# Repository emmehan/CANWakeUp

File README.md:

Work in progress

# CAN WakeUp

The intendation of this project is to create a device that will act as a Wake-Up source for CAN devices.
A microcontroller ([STM32F103](https://www.st.com/en/microcontrollers/stm32f103c8.html)) sends a cyclic CAN messages using an external CAN transceiver ([TJA1050](https://www.nxp.com/docs/en/data-sheet/TJA1050.pdf)).

This project includes the EAGLE schematic and layout files among the source code for the microcontroller.

# Project structure

## Hardware
@TODO

## Software
Big shout-out to Patrik Jaworski for his [blog post](http://regalis.com.pl/en/arm-cortex-stm32-gnulinux/) about the initial bring up of the STM32Fx.
It really helped me to get back on track after a longer absence from the STM32 device family.

The software is based on the [STM32CubeF1 MCu Package ](https://www.st.com/en/embedded-software/stm32cubef1.html) from ST Microelectronis.
The application software is based on the ARM CMSIS library for the STM32F103C8T6 device.

It is developed on Linux (Arch-Linux, Kernel 4.19.2) using the GNU ARM toolchain(gcc-arm-none-eabi-*).

---

### Build

To build the firmware run:

    make -C ./Software MAIN=FW_NAME
in directory.

The `MAIN` parameter is optional and used to define the firmware name.

It defaults to `CANWakeUp`.

---

### Flash

To flash the firmare to the controller run:

    openocd -f interface/stlink-v2-1.cfg -f target/stm32f1x.cfg -c "program ./build/$FW_NAME.hex  verify reset exit"
while substitute `$FW_NAME` to the correct firmware filename.

There are preconfigured tasks for Visual Studio Code available for Building, Cleaning, Flashing and Debugging (using the [Cortex-Debug](https://marcelball.ca/projects/cortex-debug) extension by marus25).

---

### Software Documentation

To build the documentation run (requires [Doxygen](http://doxygen.nl/)):

    make doc

The documentation will then be available in `./doc/html/index.html`.

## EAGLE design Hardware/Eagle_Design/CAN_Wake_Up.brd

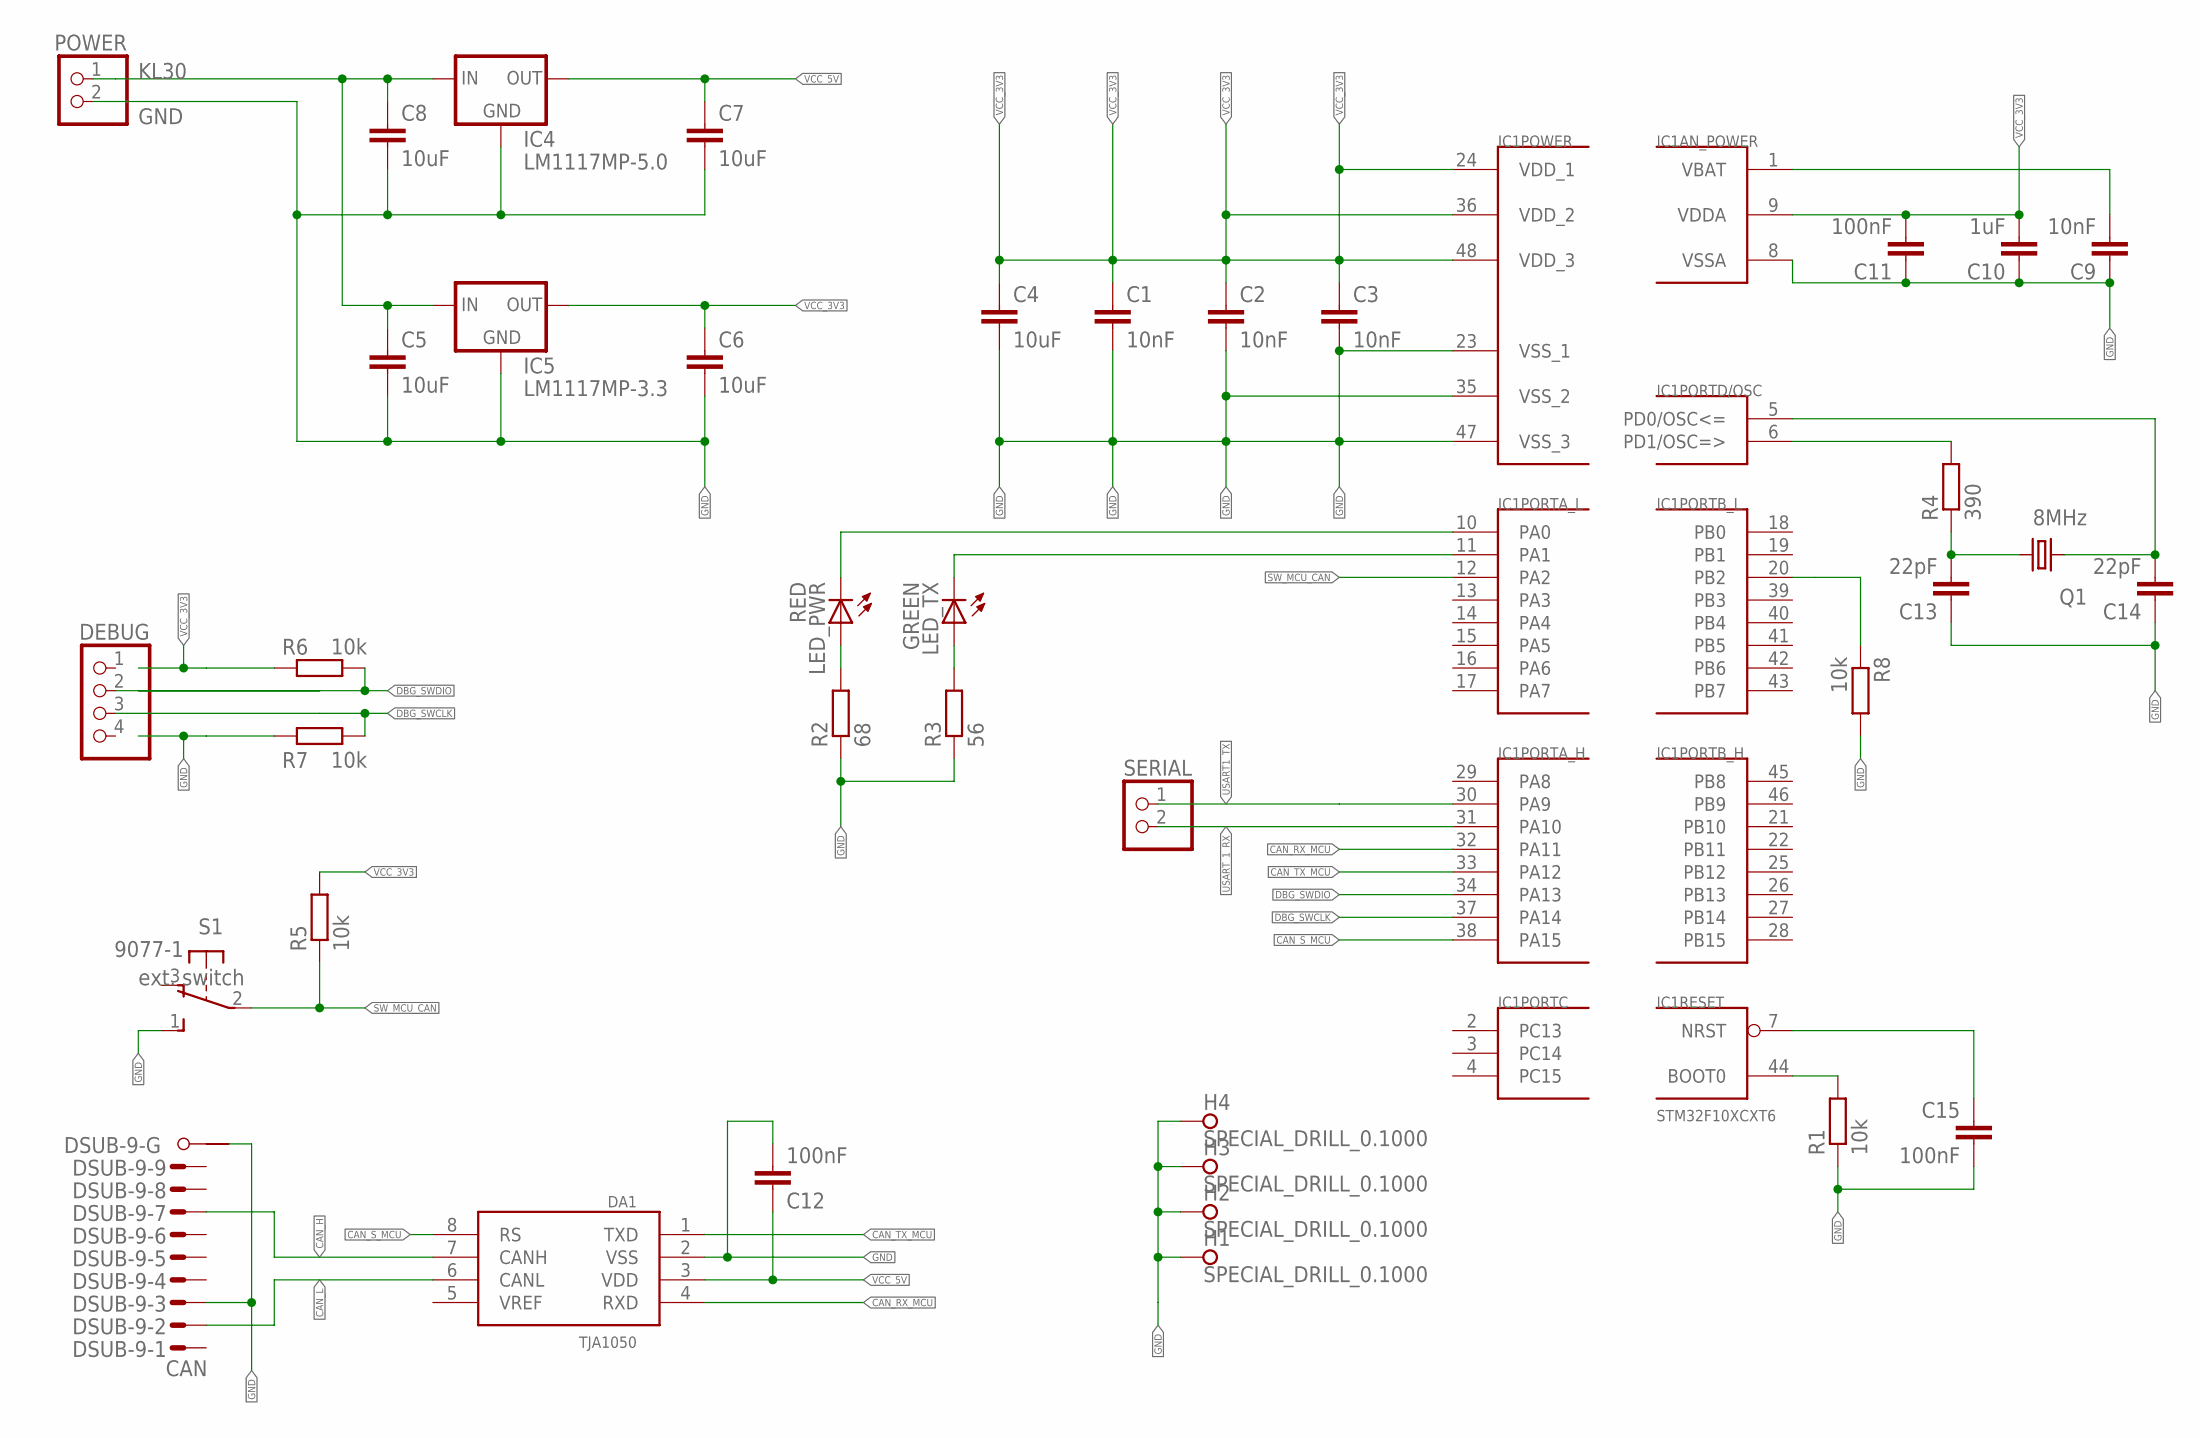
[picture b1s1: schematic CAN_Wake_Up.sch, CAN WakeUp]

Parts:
C1, C2, C3, C9: 10nF; C0805
C4, C5, C6, C7, C8: 10uF; C0805
C10: 1uF; C0805
C11, C12, C15: 100nF; C0805
C13, C14: 22pF; C0805
DA1: TJA1050; SO08
DEBUG: PINHD-1X4; 1X04
DSUB-9: CAN; M09HP
H1, H2, H3, H4: SPECIAL_DRILL_0.1000; PAD_0.1000
IC1: STM32F10XCXT6; TQFP48
IC4: LM1117MP-5.0; SOT223
IC5: LM1117MP-3.3; SOT223
LED_PWR: RED; SML0805
LED_TX: GREEN; SML0805
POWER: PINHD-1X2; 1X02
Q1: 8MHz; HC49UP
R1, R5, R6, R7, R8: 10k; R0805
R2: 68; R0805
R3: 56; R0805
R4: 390; R0805
S1: 9077-1
SERIAL: PINHD-1X2; 1X02

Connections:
CAN_H: DA1.7 (CANH), DSUB-9.7 (M)
CAN_L: DA1.6 (CANL), DSUB-9.2 (M)
CAN_RX_MCU: DA1.4 (RXD), IC1.32 (PA11)
CAN_S_MCU: DA1.8 (RS), IC1.38 (PA15)
CAN_TX_MCU: DA1.1 (TXD), IC1.33 (PA12)
DBG_SWCLK: DEBUG.3, IC1.37 (PA14), R7.1
DBG_SWDIO: DEBUG.2, IC1.34 (PA13), R6.2
GND: C1.2, C2.2, C3.2, C4.2, C5.2, C6.2, C7.2, C8.2, C9.1, C10.1, C11.1, C12.2, C13.1, C14.1, C15.2, DA1.2 (VSS), DEBUG.4, DSUB-9.3 (M), DSUB-9.G1, H1.1, H2.1, H3.1, H4.1, IC1.8 (VSSA), IC1.23 (VSS_1), IC1.35 (VSS_2), IC1.47 (VSS_3), IC4.1 (GND), IC5.1 (GND), POWER.2, R1.1, R2.1, R3.1, R7.2, R8.2, S1.1 (S)
KL30: C5.1, C8.1, IC4.3 (IN), IC5.3 (IN), POWER.1
LED_MCU_CAN: IC1.11 (PA1), LED_TX.C
LED_MCU_PWR: IC1.10 (PA0), LED_PWR.C
unnamed: IC1.44 (BOOT0), R1.2
unnamed: C9.2, IC1.1 (VBAT)
unnamed: LED_PWR.A, R2.2
unnamed: LED_TX.A, R3.2
unnamed: C13.2, Q1.2, R4.1
unnamed: C14.2, IC1.5 (PD0/OSC<=), Q1.1
unnamed: IC1.6 (PD1/OSC=>), R4.2
unnamed: IC1.20 (PB2), R8.1
unnamed: C15.1, DEBUG.5, IC1.7 (NRST)
SW_MCU_CAN: IC1.12 (PA2), R5.1, S1.2
USART1_TX: IC1.30 (PA9), SERIAL.1
USART_1_RX: IC1.31 (PA10), SERIAL.2
VCC_3V3: C1.1, C2.1, C3.1, C4.1, C6.1, C10.2, C11.2, DEBUG.1, IC1.9 (VDDA), IC1.24 (VDD_1), IC1.36 (VDD_2), IC1.48 (VDD_3), IC5.2 (OUT), IC5.4 (OUT), R5.2, R6.1
VCC_5V: C7.1, C12.1, DA1.3 (VDD), IC4.2 (OUT), IC4.4 (OUT)

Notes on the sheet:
ext. switch

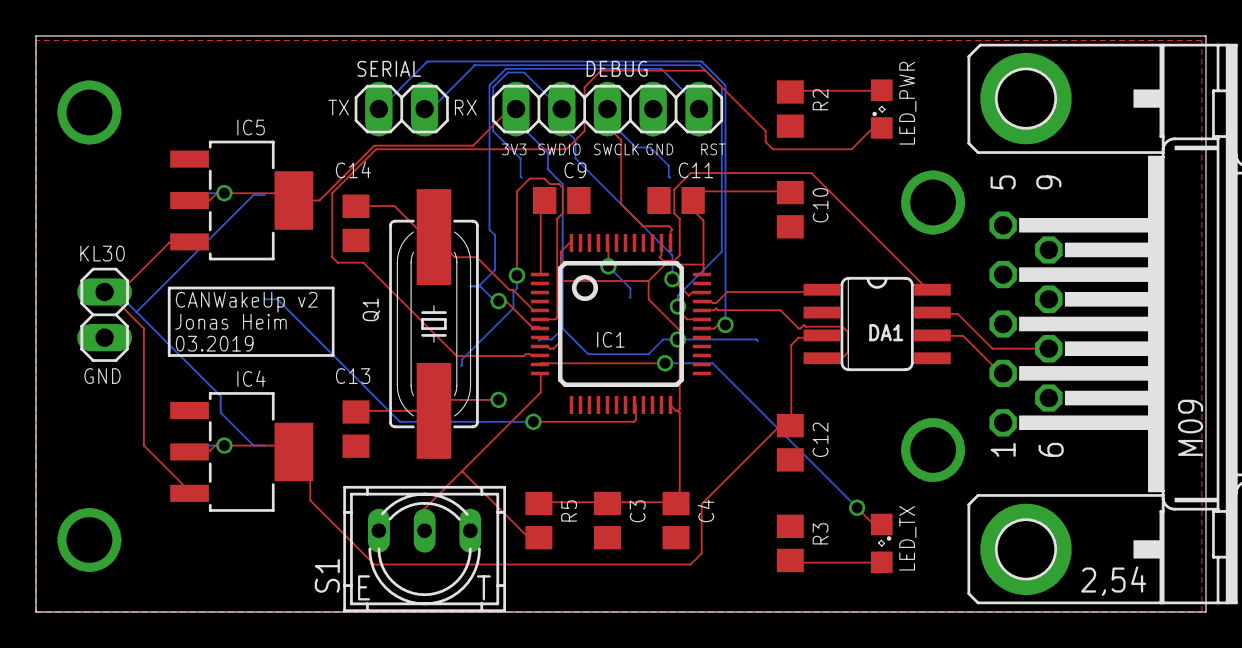
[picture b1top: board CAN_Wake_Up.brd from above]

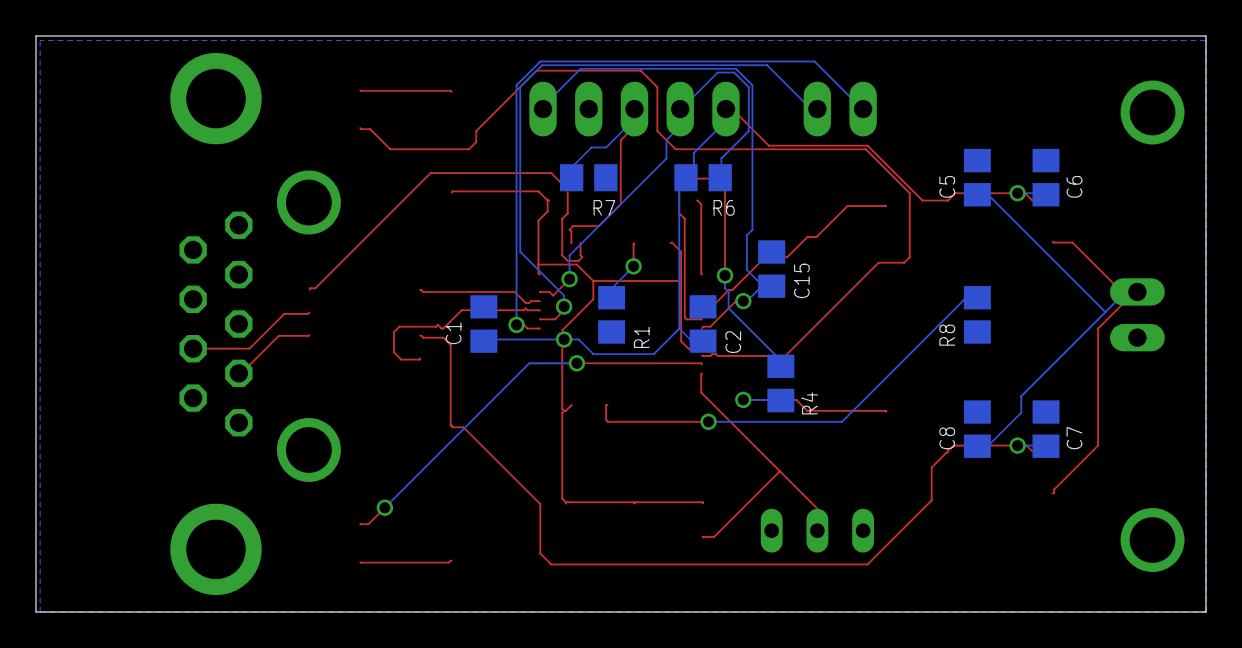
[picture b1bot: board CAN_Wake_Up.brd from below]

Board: 2 copper layers, 65.0 x 32.0 mm, 39 parts (12 on the bottom side), 25 nets.

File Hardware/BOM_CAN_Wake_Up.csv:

"Part";"Value";"Device";"Package";"Description";"MF";"MPN";"OC_FARNELL";"OC_NEWARK";"TP_SIGNAL_NAME";
"C1";"10nF";"C-EUC0805";"C0805";"CAPACITOR, European symbol";"";"";"";"";"";
"C2";"10nF";"C-EUC0805";"C0805";"CAPACITOR, European symbol";"";"";"";"";"";
"C3";"10nF";"C-EUC0805";"C0805";"CAPACITOR, European symbol";"";"";"";"";"";
"C4";"10uF";"C-EUC0805";"C0805";"CAPACITOR, European symbol";"";"";"";"";"";
"C5";"10uF";"C-EUC0805";"C0805";"CAPACITOR, European symbol";"";"";"";"";"";
"C6";"10uF";"C-EUC0805";"C0805";"CAPACITOR, European symbol";"";"";"";"";"";
"C7";"10uF";"C-EUC0805";"C0805";"CAPACITOR, European symbol";"";"";"";"";"";
"C8";"10uF";"C-EUC0805";"C0805";"CAPACITOR, European symbol";"";"";"";"";"";
"C9";"10nF";"C-EUC0805";"C0805";"CAPACITOR, European symbol";"";"";"";"";"";
"C10";"1uF";"C-EUC0805";"C0805";"CAPACITOR, European symbol";"";"";"";"";"";
"C11";"100nF";"C-EUC0805";"C0805";"CAPACITOR, European symbol";"";"";"";"";"";
"C12";"100nF";"C-EUC0805";"C0805";"CAPACITOR, European symbol";"";"";"";"";"";
"C13";"22pF";"C-EUC0805";"C0805";"CAPACITOR, European symbol";"";"";"";"";"";
"C14";"22pF";"C-EUC0805";"C0805";"CAPACITOR, European symbol";"";"";"";"";"";
"DA1";"TJA1050";"TJA1050";"SO08";"High speed CAN transceiver";"";"";"";"";"";
"DBG_GND";"TPB1,27";"TPB1,27";"B1,27";"Test pad";"";"";"";"";"";
"DBG_SWCLK";"TPB1,27";"TPB1,27";"B1,27";"Test pad";"";"";"";"";"";
"DBG_SWDIO";"TPB1,27";"TPB1,27";"B1,27";"Test pad";"";"";"";"";"";
"DBG_VCC_3V3";"TPB1,27";"TPB1,27";"B1,27";"Test pad";"";"";"";"";"";
"DSUB-9";"CAN";"M09HPS";"M09HP";"SUB-D";"";"";"unknown";"unknown";"";
"GND";"";"PINHD-1X1";"1X01";"PIN HEADER";"";"";"";"";"";
"H1";"SPECIAL_DRILL_0.1000";"SPECIAL_DRILL_0.1000";"PAD_0.1000";"Special drills";"";"";"";"";"";
"H2";"SPECIAL_DRILL_0.1000";"SPECIAL_DRILL_0.1000";"PAD_0.1000";"Special drills";"";"";"";"";"";
"H3";"SPECIAL_DRILL_0.1000";"SPECIAL_DRILL_0.1000";"PAD_0.1000";"Special drills";"";"";"";"";"";
"H4";"SPECIAL_DRILL_0.1000";"SPECIAL_DRILL_0.1000";"PAD_0.1000";"Special drills";"";"";"";"";"";
"IC1";"STM32F10XCXT6";"STM32F10XCXT6";"TQFP48";"ST STM32F101/103 48pin LQFP";"";"";"";"";"";
"IC4";"LM1117MP-5.0";"LM1117MP-5.0";"SOT223";"800mA Low-Dropout Linear Regulator";"Texas Instruments";"LM1117MP-5.0";"9778209";"28X3417";"";
"IC5";"LM1117MP-3.3";"LM1117MP-3.3";"SOT223";"800mA Low-Dropout Linear Regulator";"Texas Instruments";"LM1117MP-3.3";"9778195";"28X3416";"";
"KL30";"";"PINHD-1X1";"1X01";"PIN HEADER";"";"";"";"";"";
"LED_PWR";"RED";"LEDSML0805";"SML0805";"LED";"";"";"";"";"";
"LED_TX";"GREEN";"LEDSML0805";"SML0805";"LED";"";"";"";"";"";
"Q1";"8MHz";"CRYSTALHC49UP";"HC49UP";"CRYSTAL";"";"";"unknown";"unknown";"";
"R1";"10k";"R-EU_R0805";"R0805";"RESISTOR, European symbol";"";"";"";"";"";
"R2";"68";"R-EU_R0805";"R0805";"RESISTOR, European symbol";"";"";"";"";"";
"R3";"56";"R-EU_R0805";"R0805";"RESISTOR, European symbol";"";"";"";"";"";
"R4";"390";"R-EU_R0805";"R0805";"RESISTOR, European symbol";"";"";"";"";"";
"R5";"10k";"R-EU_R0805";"R0805";"RESISTOR, European symbol";"";"";"";"";"";
"R6";"10k";"R-EU_R0805";"R0805";"RESISTOR, European symbol";"";"";"";"";"";
"R7";"10k";"R-EU_R0805";"R0805";"RESISTOR, European symbol";"";"";"";"";"";
"R8";"10k";"R-EU_R0805";"R0805";"RESISTOR, European symbol";"";"";"";"";"";
"S1";"9077-1";"9077-1";"9077-1";"MARQUARDT SWITCH 9077.0100";"";"";"";"";"";

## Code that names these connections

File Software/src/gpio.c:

/**************************************************************************//**
 * @file     gpio.c
 * @brief    Implementation file of the GPIO module.
 * @version  V1.0
 * @date     03.03.2019
 ******************************************************************************/

/*
Application for interfacing a TJA1050 CAN transceiver with a STM32F103C8T6 MCU.
Copyright (C) 2019  Jonas Heim
This program is free software: you can redistribute it and/or modify
it under the terms of the GNU General Public License as published by
the Free Software Foundation, either version 3 of the License, or
(at your option) any later version.
This program is distributed in the hope that it will be useful,
but WITHOUT ANY WARRANTY; without even the implied warranty of
MERCHANTABILITY or FITNESS FOR A PARTICULAR PURPOSE.  See the
GNU General Public License for more details.
You should have received a copy of the GNU General Public License
along with this program.  If not, see <http://www.gnu.org/licenses/>.
*/

#include "gpio.h"

/**
  \brief    Initializes the gpio peripherals.
  \details  Enabled clock for GPIO Port A.
            Configures Port A Pin 0 as Push/Pull Output (Signal LED_RED).
            Configures Port A Pin 1 as Push/Pull Output (Signal LED_GREEN).
            Configures Port A Pin 2 as FLoating Input (Signal SWITCH).
            Configures Port A Pin 8 as Alternative function SYSCLK output (Signal MCO).
            Configures Port A Pin 10 as Push/Pull Output (Signal CAN_SILENT_MODE).
            Configures Port A Pin 11 as Alternative function (Signal CAN_RX).
            Configures Port A Pin 12 as Alternative function (Signal LED_TX).
 */
void gpio_init()
{

    /* enable clock for port A */
    RCC->APB2ENR |= RCC_APB2ENR_IOPAEN;


    /************************************************
     * Configure Pin PA0 as GPIO output (LED RED)
     ************************************************/
    GPIOA->CRL |= (GPIO_CRL_MODE0_0);
    GPIOA->CRL &= ~(GPIO_CRL_MODE0_1);
    GPIOA->CRL &= ~(GPIO_CRL_CNF0_1 | GPIO_CRL_CNF0_0);

    /* set initially to high -> LED off */
    GPIOA->BSRR |= GPIO_BSRR_BS0;

    /************************************************
     * Configure Pin PA1 as GPIO output (LED GREEN)
     ************************************************/
    GPIOA->CRL |= (GPIO_CRL_MODE1_0);
    GPIOA->CRL &= ~(GPIO_CRL_MODE1_1);
    GPIOA->CRL &= ~(GPIO_CRL_CNF1_1 | GPIO_CRL_CNF1_0);
    
    /* set initially to high -> LED off */
    GPIOA->BSRR |= GPIO_BSRR_BS1;

    /************************************************
     * Configure Pin PA2 as GPIO input (SWITCH)
     ************************************************/
    GPIOA->CRL &= ~(GPIO_CRL_MODE2_1 | GPIO_CRL_MODE2_0);
    GPIOA->CRL &= ~(GPIO_CRL_CNF2_1);
    GPIOA->CRL |= GPIO_CRL_CNF2_0;

    /************************************************
     * Configure Pin PA8 as alternate function (MCO)
     ************************************************/
    GPIOA->CRH  |= (GPIO_CRH_MODE8_1 | GPIO_CRH_MODE8_0);
    GPIOA->CRH &= ~(GPIO_CRH_CNF8);
    GPIOA->CRH |= (GPIO_CRH_CNF8_1);

    /*****************************************************
     * Configure Pin PA10 as GPIO output (CAN_SILENT_MODE)
     *****************************************************/
    GPIOA->CRH |= (GPIO_CRH_MODE10_1 | GPIO_CRH_MODE10_0);
    GPIOA->CRH &= ~(GPIO_CRH_CNF10_1 | GPIO_CRH_CNF10_0);

    /*****************************************************
     * Configure Pin PA11 as alternate function (CAN_RX)
     *****************************************************/
    GPIOA->CRH &= ~(GPIO_CRH_MODE11_1 | GPIO_CRH_MODE11_0);
    GPIOA->CRH &= ~(GPIO_CRH_CNF11_1);
    GPIOA->CRH |= (GPIO_CRH_CNF11_0);

    /*****************************************************
     * Configure Pin PA12 as alternate function (CAN_TX)
     *****************************************************/
    GPIOA->CRH &= ~(GPIO_CRH_MODE12_1);
    GPIOA->CRH |= GPIO_CRH_MODE12_0;
    GPIOA->CRH |= (GPIO_CRH_CNF12_1);
    GPIOA->CRH &= ~(GPIO_CRH_CNF12_0);
}

/**
  \brief    Set output value of signal LED_RED.
  \details  Set output value of Port A Pin 0.
  \param[in] _new_state The new output value of the signal.
 */
void gpio_set_led_red(BITACTION_t _new_state)
{
    if(BITACTION_RESET == _new_state)
    {
        GPIOA->BSRR |= GPIO_BSRR_BR0; //bit reset (to low)
    }
    else if(BITACTION_SET == _new_state)
    {
        GPIOA->BSRR |= GPIO_BSRR_BS0; //bit set (to high)
    }
}

/**
  \brief    Set output value of signal LED_GREEN.
  \details  Set output value of Port A Pin 1.
  \param[in] _new_state The new output value of the signal.
 */
void gpio_set_led_green(BITACTION_t _new_state)
{
    if(BITACTION_RESET == _new_state)
    {
        GPIOA->BSRR |= GPIO_BSRR_BR1; //bit reset (to low)
    }
    else if(BITACTION_SET == _new_state)
    {
        GPIOA->BSRR |= GPIO_BSRR_BS1; //bit set (to high)
    }
}

/**
  \brief    Set output value of signal CAN_SILENT_MODE.
  \details  Set output value of Port A Pin 10.
  \param[in] _new_state The new output value of the signal.
 */
void gpio_set_can_silent_mode(BITACTION_t _new_state)
{
    if(BITACTION_RESET == _new_state)
    {
        GPIOA->BSRR |= GPIO_BSRR_BR10; //bit reset (to low)
    }
    else if(BITACTION_SET == _new_state)
    {
        GPIOA->BSRR |= GPIO_BSRR_BS10; //bit set (to high)
    }
}

/**
  \brief    Get input value of signal SWITCH.
  \details  Get output value of Port A Pin 2.
  \return   Returns the current value of the signal (not debounced!).
 */
BITACTION_t gpio_read_button(void)
{
    static uint32_t portvals = 0;
    BITACTION_t retval = BITACTION_RESET;
    
    /* read button state */
    portvals = GPIOA->IDR;
    if(portvals & (GPIO_IDR_IDR2))
    {
        retval = BITACTION_SET;
    }

    return retval;
}

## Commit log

2018-12-17 Initial commit. Added Eagle project and a first draft of the schematic and BOM.
2018-12-17 Added README.md file.
2018-12-17 Updated schematic.
2018-12-17 Added datasheet for CAN transceiver TJA1051.
2018-12-17 Added .gitignore for schematic subdir to exclude temp. Eagle files. Updated BOM. Added Eagle BOM textfile. Updated schematic. Added Debug interface.
2018-12-17 Reworked schematic. Added GND signal.
2018-12-19 Renamed schematic and layout directory. Updated Schematic, replaced crystal with SMD variant. Added initial board layout file.
2018-12-20 Moved schematic .pdf.
2018-12-27 Added .gitignore in build directory to ignore all build results but maintain the directory.
2018-12-27 Fixed wrong PLL/SYSCLK configuration - working now @ 32MHz SYSCLK. Added Clock-Out (MCO pin) to provide the SYSCLK (32MHz) on Pin A8. Added simple LED blinking on Pin A9. Replaced wrong ARM core head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
2019-01-09 Started on PCB layout.
2019-01-10 Continued on layout. Not yet fully routable. PCB need to be resized.
2019-01-12 Finished board layout. First order at seeedstudio.com
2019-02-03 New version. Added Eagle BOM (.csv) file.
2019-02-06 Added compiler option to include debug symbols. in .elf file.
2019-02-07 Updated schematic PDF.
2019-02-14 Updated GPIOs to new board. Small blinking application.
2019-02-20 LED update in SW
2019-02-20 Added GPIO initialization for CAN signals. Added software licensing. Removed build output directory from tracking.
2019-02-20 Started with implementing SysTick timer.
2019-03-03 A whole lot of updates... Added Link to Cortex-Debug extension for VSCode in README.md. Added Debug-Task for VSCode using said Cortex-Debug extension. Added STM32F10x Cortex-M3 Programming Manual. Fi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
2019-03-03 Added doxygen documentation. Documentation can now be built by make. Added first documentation to source. README.md includes now sections about building the documentation.
2019-03-05 Added LED blinking in TIM2 interrupt routine. Started with initialization of CAN peripheral.
2019-03-10 Fixed CAN signals (Tx and Rx switched). Added CAN bit timing configuration for 500kbit/s.
2019-03-10 Fixed ignores
2019-03-10 Fixed ignores again
2019-03-13 Fixed GPIO initialization of SWITCH input and CAN RX/TX. Switch will now disable/enable LED blinking.
2019-03-26 Resolved issue that can_init() hangs,
2019-04-28 Latest hardware revision: rev2
2019-06-10 HAL Library integrated. Makefile updated. VSCode Flash and Debug task now configured for STLinkV2.
2019-06-11 Fixed task.json to use environment variable $env:APP_NAME in make call.
2019-06-11 Added STM32 HAL documents.
2019-06-12 Removed clean from all target in makefile. Fixed usage of application name in Flash task in tasks.json. Added correct device define. Added UART test. Added switch test.
2019-06-25 Renamed user include directory to inc. Hopefully fixed the VSCode Flash task finally.
2019-06-25 Added .gitignore for IPCH directory.
2019-06-26 Added BSP. CAN TX is finally working 500kbit/s! :)
2019-06-27 CAN working bidirectional. Sends cyclic message every 100ms. A received message is echoed back with ID+1. Minimal CAN Error handling. Removed stm32f1xx_hal_msp.c file.
2019-06-27 CANWakeUp working. Sends a WakeUp message every 1s. Switched mode to Loopback, since DUT is sending CAN-FD messages, trigger CAN errors.
2019-07-01 Added PVD (programmable voltage detector). When a supply voltage of <2.9V is reached, an interrupt is triggered.
2019-07-01 FreeRTOS integrated. Systick is still used by HAL, but SysTickHandler calls osSystickHandler.
2019-07-05 Added FreeRTOS Tracing for Percepio. CAN not working on boards - investigation needed.
2019-08-09 Fixed directory in include path for BSP files.
2019-08-09 Fixed directory to run make from.
2019-08-09 Intendation in README.md
2019-08-09 Add build status of Jenkins CI to README
